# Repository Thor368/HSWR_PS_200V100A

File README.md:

# HSWR_PS_200V100A
This is the power stage matching the CPU board. This power stage is designed for an operating voltage of up to 200V and a maximum RMS current of up to 100A.

This project is depricated and was replaced by the HSWR2:
https://github.com/Thor368/HSWR_V2

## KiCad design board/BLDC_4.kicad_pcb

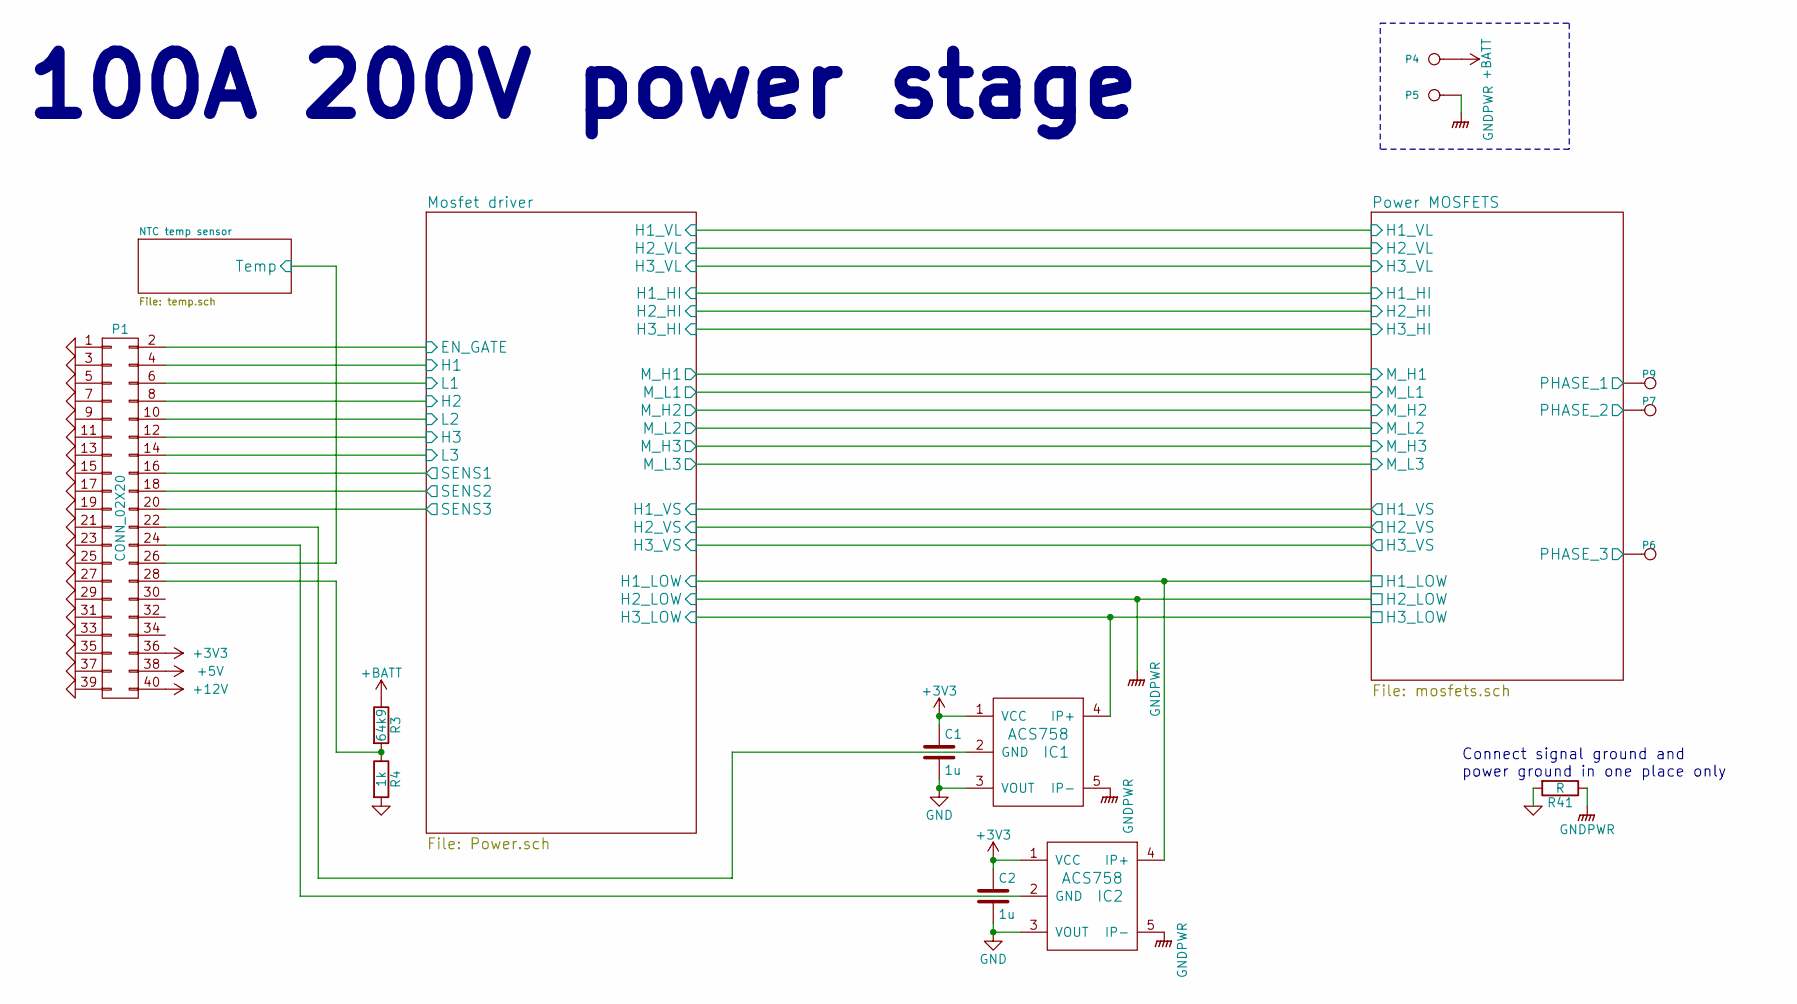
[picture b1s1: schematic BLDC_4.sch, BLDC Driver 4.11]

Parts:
C1, C2: 1u; C_0805
IC1, IC2: ACS758; CB-PFF
P1: CONN_02X20; XG4A_40
P4: IN+; MountingHole_6.5mm_Pad_Via
P5: IN-; MountingHole_6.5mm_Pad_Via
P6: MOTOR1; MountingHole_6.5mm_Pad_Via
P7: MOTOR2; MountingHole_6.5mm_Pad_Via
P9: MOTOR3; MountingHole_6.5mm_Pad_Via
R3: 64k9; R_0805
R4: 1k; R_0805
R41: R; R_0805

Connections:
+3V3: C1.1, C2.1, IC1.1 (VCC), IC2.1 (VCC), P1.36; also elsewhere on the board
+12V: P1.40; also elsewhere on the board
+BATT: P4.1, R3.1; also elsewhere on the board
/Mosfet driver/EN_GATE: P1.2; also elsewhere on the board
/Mosfet driver/H1: P1.4; also elsewhere on the board
/Mosfet driver/H1_LOW: IC2.4 (IP+); also elsewhere on the board
/Mosfet driver/H1_VS: P9.1; also elsewhere on the board
/Mosfet driver/H2: P1.8; also elsewhere on the board
/Mosfet driver/H2_VS: P7.1; also elsewhere on the board
/Mosfet driver/H3: P1.12; also elsewhere on the board
/Mosfet driver/H3_LOW: IC1.4 (IP+); also elsewhere on the board
/Mosfet driver/H3_VS: P6.1; also elsewhere on the board
/Mosfet driver/L1: P1.6; also elsewhere on the board
/Mosfet driver/L2: P1.10; also elsewhere on the board
/Mosfet driver/L3: P1.14; also elsewhere on the board
/Mosfet driver/SENS1: P1.16; also elsewhere on the board
/Mosfet driver/SENS2: P1.18; also elsewhere on the board
/Mosfet driver/SENS3: P1.20; also elsewhere on the board
/NTC temp sensor/Temp: P1.26; also elsewhere on the board
GND: C1.2, C2.2, IC1.3 (VOUT), IC2.3 (VOUT), P1.1, P1.3, P1.5, P1.7, P1.9, P1.11, P1.13, P1.15, P1.17, P1.19, P1.21, P1.23, P1.25, P1.27, P1.29, P1.31, P1.33, P1.35, P1.37, P1.39, R4.2, R41.2; also elsewhere on the board
GNDPWR: IC1.5 (IP-), IC2.5 (IP-), P5.1, R41.1; also elsewhere on the board
unnamed: IC1.2 (GND), P1.22
unnamed: IC2.2 (GND), P1.24
unnamed: P1.28, R3.2, R4.1

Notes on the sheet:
100A 200V power stage
Connect signal ground and power ground in one place only

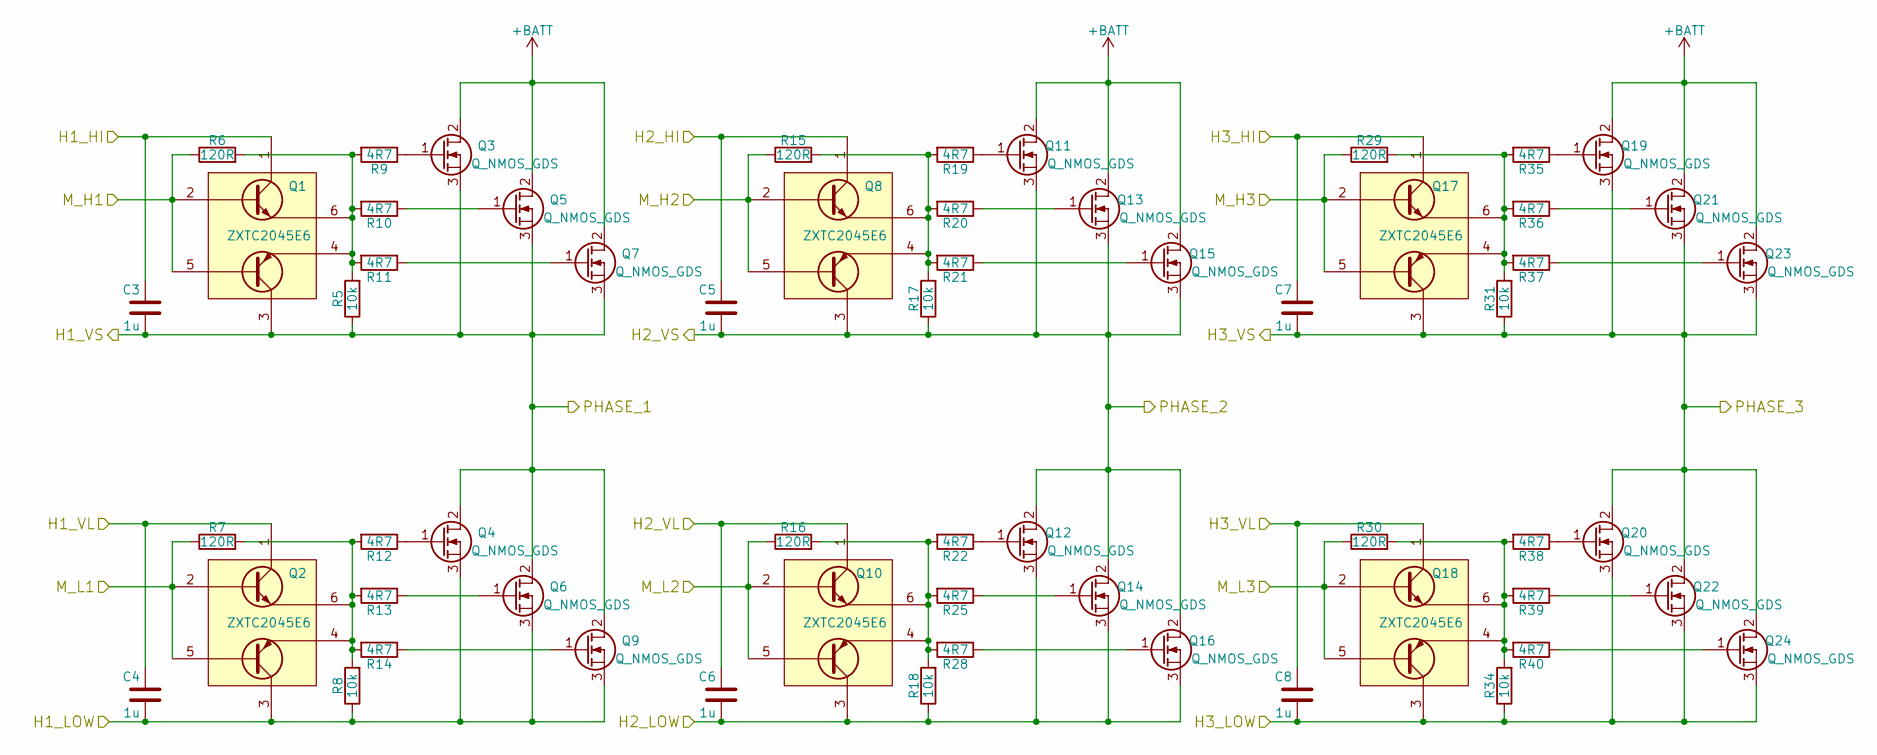
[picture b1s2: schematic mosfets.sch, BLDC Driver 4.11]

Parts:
C3, C4, C5, C6, C7, C8: 1u; C_0805
Q1, Q2, Q8, Q10, Q17, Q18: ZXTC2045E6; SOT-23-6
Q3, Q4, Q5, Q6, Q7, Q9, Q11, Q12, Q13, Q14, Q15, Q16, Q19, Q20, Q21, Q22, Q23, Q24: Q_NMOS_GDS; TO-264_flat_reverse
R5, R8, R17, R18, R31, R34: 10k; R_0805
R6, R7, R15, R16, R29, R30: 120R; R_0805
R9, R10, R11, R12, R13, R14, R19, R20, R21, R22, R25, R28, R35, R36, R37, R38, R39, R40: 4R7; R_0805

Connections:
+12V: C4.1, C6.1, C8.1, Q2.1 (C1), Q10.1 (C1), Q18.1 (C1); also elsewhere on the board
+BATT: Q3.2 (D), Q5.2 (D), Q7.2 (D), Q11.2 (D), Q13.2 (D), Q15.2 (D), Q19.2 (D), Q21.2 (D), Q23.2 (D); also elsewhere on the board
/Mosfet driver/H1_HI: C3.1, Q1.1 (C1); also elsewhere on the board
/Mosfet driver/H1_LOW: C4.2, Q2.3 (C2), Q4.3 (S), Q6.3 (S), Q9.3 (S), R8.1; also elsewhere on the board
/Mosfet driver/H1_VS: C3.2, Q1.3 (C2), Q3.3 (S), Q4.2 (D), Q5.3 (S), Q6.2 (D), Q7.3 (S), Q9.2 (D), R5.1; also elsewhere on the board
/Mosfet driver/H2_HI: C5.1, Q8.1 (C1); also elsewhere on the board
/Mosfet driver/H2_VS: C5.2, Q8.3 (C2), Q11.3 (S), Q12.2 (D), Q13.3 (S), Q14.2 (D), Q15.3 (S), Q16.2 (D), R17.1; also elsewhere on the board
/Mosfet driver/H3_HI: C7.1, Q17.1 (C1); also elsewhere on the board
/Mosfet driver/H3_LOW: C8.2, Q18.3 (C2), Q20.3 (S), Q22.3 (S), Q24.3 (S), R34.1; also elsewhere on the board
/Mosfet driver/H3_VS: C7.2, Q17.3 (C2), Q19.3 (S), Q20.2 (D), Q21.3 (S), Q22.2 (D), Q23.3 (S), Q24.2 (D), R31.1; also elsewhere on the board
/Mosfet driver/M_H1: Q1.2 (B1), Q1.5 (B2), R6.1; also elsewhere on the board
/Mosfet driver/M_H2: Q8.2 (B1), Q8.5 (B2), R15.1; also elsewhere on the board
/Mosfet driver/M_H3: Q17.2 (B1), Q17.5 (B2), R29.1; also elsewhere on the board
/Mosfet driver/M_L1: Q2.2 (B1), Q2.5 (B2), R7.1; also elsewhere on the board
/Mosfet driver/M_L2: Q10.2 (B1), Q10.5 (B2), R16.1; also elsewhere on the board
/Mosfet driver/M_L3: Q18.2 (B1), Q18.5 (B2), R30.1; also elsewhere on the board
GNDPWR: C6.2, Q10.3 (C2), Q12.3 (S), Q14.3 (S), Q16.3 (S), R18.1; also elsewhere on the board
unnamed: Q1.4 (E2), Q1.6 (E1), R5.2, R6.2, R9.2, R10.2, R11.2
unnamed: Q2.4 (E2), Q2.6 (E1), R7.2, R8.2, R12.2, R13.2, R14.2
unnamed: Q3.1 (G), R9.1
unnamed: Q4.1 (G), R12.1
unnamed: Q5.1 (G), R10.1
unnamed: Q6.1 (G), R13.1
unnamed: Q7.1 (G), R11.1
unnamed: Q8.4 (E2), Q8.6 (E1), R15.2, R17.2, R19.2, R20.2, R21.2
unnamed: Q9.1 (G), R14.1
unnamed: Q10.4 (E2), Q10.6 (E1), R16.2, R18.2, R22.2, R25.2, R28.2
unnamed: Q11.1 (G), R19.1
unnamed: Q12.1 (G), R22.1
unnamed: Q13.1 (G), R20.1
unnamed: Q14.1 (G), R25.1
unnamed: Q15.1 (G), R21.1
unnamed: Q16.1 (G), R28.1
unnamed: Q17.4 (E2), Q17.6 (E1), R29.2, R31.2, R35.2, R36.2, R37.2
unnamed: Q18.4 (E2), Q18.6 (E1), R30.2, R34.2, R38.2, R39.2, R40.2
unnamed: Q19.1 (G), R35.1
unnamed: Q20.1 (G), R38.1
unnamed: Q21.1 (G), R36.1
unnamed: Q22.1 (G), R39.1
unnamed: Q23.1 (G), R37.1
unnamed: Q24.1 (G), R40.1

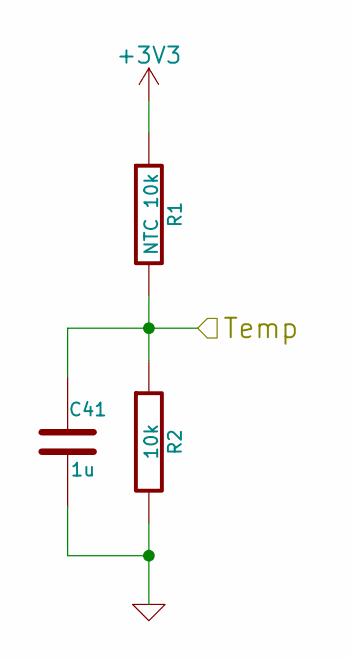
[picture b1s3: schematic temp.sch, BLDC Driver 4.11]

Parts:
C41: 1u; C_0805
R1: NTC 10k; R_0603
R2: 10k; R_0805

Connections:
+3V3: R1.1; also elsewhere on the board
/NTC temp sensor/Temp: C41.1, R1.2, R2.1; also elsewhere on the board
GND: C41.2, R2.2; also elsewhere on the board

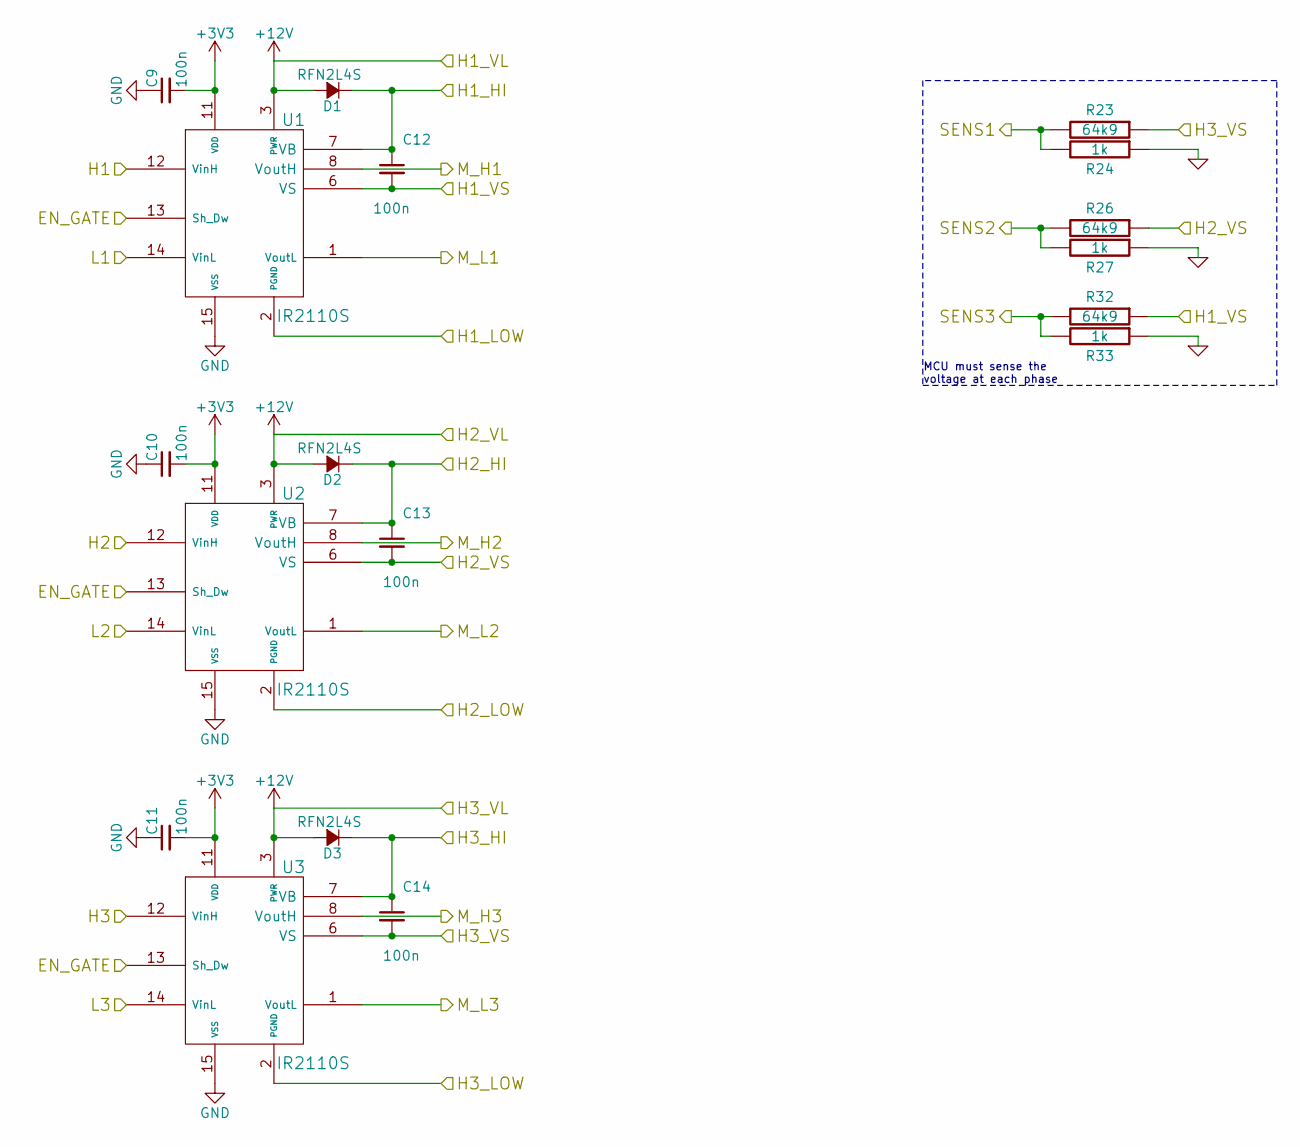
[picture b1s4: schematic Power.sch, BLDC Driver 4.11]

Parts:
C9, C10, C11, C12, C13, C14: 100n; C_0805
D1, D2, D3: RFN2L4S; SMA_Standard
R23, R26, R32: 64k9; R_0805
R24, R27, R33: 1k; R_0805
U1, U2, U3: IR2110S; SOIC-16_7.5x10.3mm_Pitch1.27mm

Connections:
+3V3: C9.2, C10.2, C11.2, U1.11 (VDD), U2.11 (VDD), U3.11 (VDD); also elsewhere on the board
+12V: D1.2 (A), D2.2 (A), D3.2 (A), U1.3 (PWR), U2.3 (PWR), U3.3 (PWR); also elsewhere on the board
/Mosfet driver/EN_GATE: U1.13 (Sh_Dw), U2.13 (Sh_Dw), U3.13 (Sh_Dw); also elsewhere on the board
/Mosfet driver/H1: U1.12 (VinH); also elsewhere on the board
/Mosfet driver/H1_HI: C12.1, D1.1 (K), U1.7 (VB); also elsewhere on the board
/Mosfet driver/H1_LOW: U1.2 (PGND); also elsewhere on the board
/Mosfet driver/H1_VS: C12.2, R32.1, U1.6 (VS); also elsewhere on the board
/Mosfet driver/H2: U2.12 (VinH); also elsewhere on the board
/Mosfet driver/H2_HI: C13.1, D2.1 (K), U2.7 (VB); also elsewhere on the board
/Mosfet driver/H2_VS: C13.2, R26.1, U2.6 (VS); also elsewhere on the board
/Mosfet driver/H3: U3.12 (VinH); also elsewhere on the board
/Mosfet driver/H3_HI: C14.1, D3.1 (K), U3.7 (VB); also elsewhere on the board
/Mosfet driver/H3_LOW: U3.2 (PGND); also elsewhere on the board
/Mosfet driver/H3_VS: C14.2, R23.1, U3.6 (VS); also elsewhere on the board
/Mosfet driver/L1: U1.14 (VinL); also elsewhere on the board
/Mosfet driver/L2: U2.14 (VinL); also elsewhere on the board
/Mosfet driver/L3: U3.14 (VinL); also elsewhere on the board
/Mosfet driver/M_H1: U1.8 (VoutH); also elsewhere on the board
/Mosfet driver/M_H2: U2.8 (VoutH); also elsewhere on the board
/Mosfet driver/M_H3: U3.8 (VoutH); also elsewhere on the board
/Mosfet driver/M_L1: U1.1 (VoutL); also elsewhere on the board
/Mosfet driver/M_L2: U2.1 (VoutL); also elsewhere on the board
/Mosfet driver/M_L3: U3.1 (VoutL); also elsewhere on the board
/Mosfet driver/SENS1: R23.2, R24.2; also elsewhere on the board
/Mosfet driver/SENS2: R26.2, R27.2; also elsewhere on the board
/Mosfet driver/SENS3: R32.2, R33.2; also elsewhere on the board
GND: C9.1, C10.1, C11.1, R24.1, R27.1, R33.1, U1.15 (VSS), U2.15 (VSS), U3.15 (VSS); also elsewhere on the board
GNDPWR: U2.2 (PGND); also elsewhere on the board

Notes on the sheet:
MCU must sense the voltage at each phase

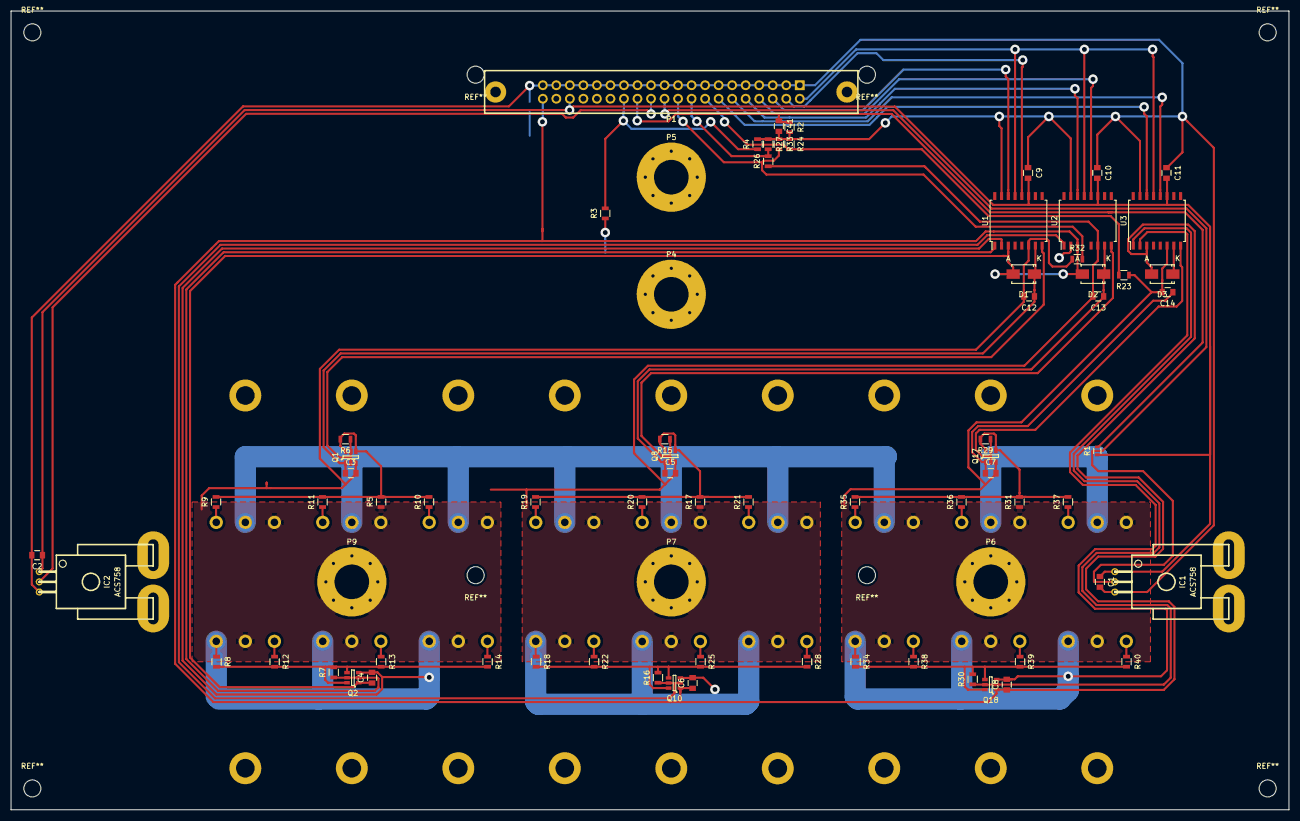
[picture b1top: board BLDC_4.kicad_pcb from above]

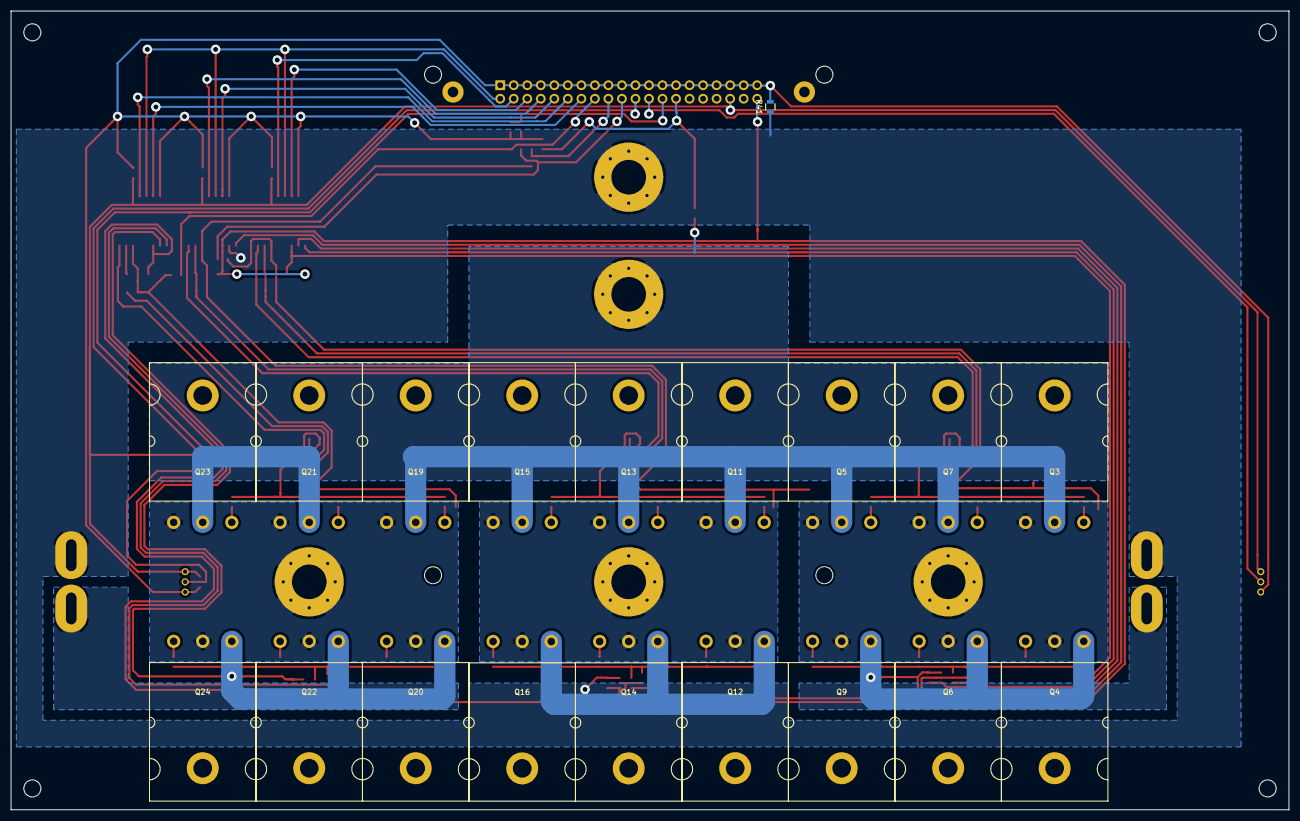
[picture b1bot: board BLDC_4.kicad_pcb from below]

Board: 2 copper layers, 240.0 x 150.0 mm, 94 parts (19 on the bottom side), 57 nets.

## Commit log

2016-06-03 - initial commit of first iteration
2016-06-03 few words about specs
2016-06-14 - implemented complementary transistor package - started layout
2016-06-15 - preliminary finish of layout
2016-06-23 - added mounting holes - added local zero - added outline
2017-11-29 Update README.md
    - added deprication note and link to HSWR2
